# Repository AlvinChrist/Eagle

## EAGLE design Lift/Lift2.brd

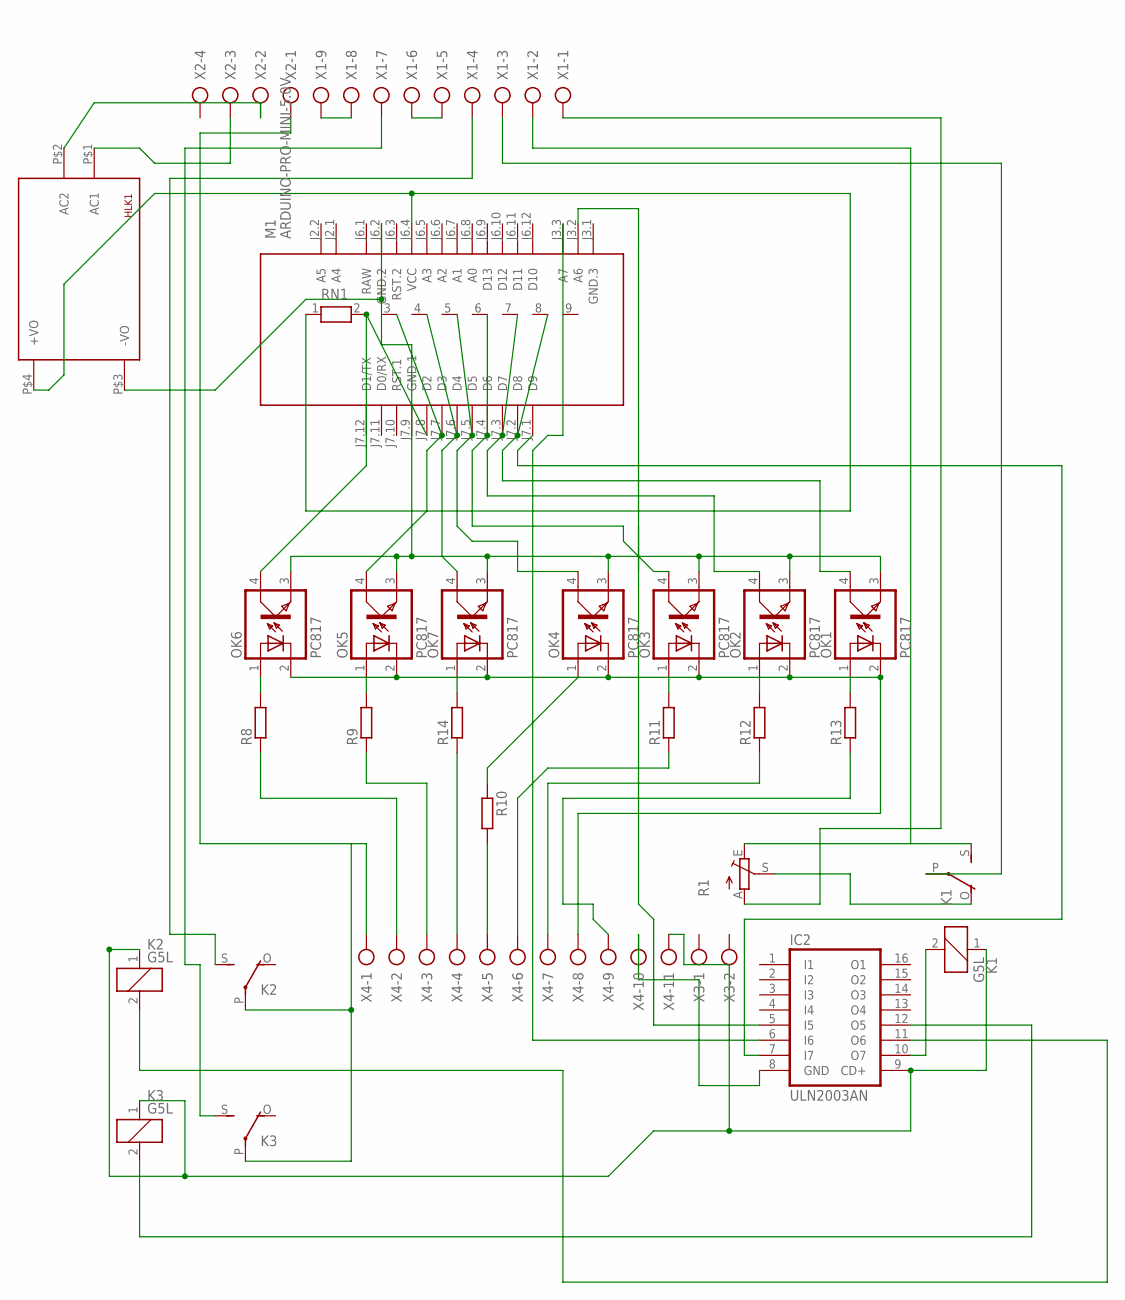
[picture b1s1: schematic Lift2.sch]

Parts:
HLK1: HLK-PM013W; HLK-PM01
IC2: ULN2003AN; DIL16
K1, K2, K3: G5L; G5LE
M1: ARDUINO-PRO-MINI-5.0V; ARDUINO-PRO-MINI
OK1, OK2, OK3, OK4, OK5, OK6, OK7: PC817; DIL04
R1: TRIM_EU-CA6V; CA6V
R8, R9, R10, R11, R12, R13, R14: R-EU_0204/7; 0204/7
RN1: RN08; RN-9
X1: AK300/9
X2: AK300/4
X3: AK300/2
X4: AK300/11

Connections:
5V: HLK1.P$4 (+VO), M1.J6.4 (VCC), RN1.1
12V: IC2.9 (CD+), K1.1, K2.1, K3.1, X4.11
24V: K2.P, K3.P, X2.1, X4.1
GND1: HLK1.P$3 (-VO), M1.J6.2 (GND.2), M1.J7.9 (GND.1), OK1.3 (EMIT), OK2.3 (EMIT), OK3.3 (EMIT), OK4.3 (EMIT), OK5.3 (EMIT), OK6.3 (EMIT), OK7.3 (EMIT)
GND2: OK1.2 (C), OK2.2 (C), OK3.2 (C), OK4.2 (C), OK5.2 (C), OK6.2 (C), OK7.2 (C), X4.8
GND3: IC2.8 (GND), X4.10
L: HLK1.P$1 (AC1), X2.3
N: HLK1.P$2 (AC2), X2.2
unnamed: OK2.1 (A), R12.2
unnamed: OK1.1 (A), R13.2
unnamed: OK3.1 (A), R11.2
unnamed: R10.2, X4.5
unnamed: OK7.1 (A), R14.2
unnamed: R14.1, X4.4
unnamed: IC2.10 (O7), K1.2
unnamed: M1.J7.7 (D3), OK5.4 (COL), RN1.3
unnamed: M1.J7.5 (D5), OK4.4 (COL), RN1.5
unnamed: M1.J7.4 (D6), OK3.4 (COL), RN1.6
unnamed: K1.O, R1.S
unnamed: M1.J7.6 (D4), OK7.4 (COL), RN1.4
unnamed: K1.S, R1.E, X1.2
unnamed: K1.P, X1.3
unnamed: R8.1, X4.2
unnamed: R9.1, X4.3
unnamed: R11.1, X4.6
unnamed: M1.J7.3 (D7), OK2.4 (COL), RN1.7
unnamed: OK5.1 (A), R9.2
unnamed: R13.1, X4.9
unnamed: X1.5, X1.6
unnamed: IC2.12 (O5), K3.2
unnamed: R12.1, X4.7
unnamed: M1.J7.2 (D8), OK1.4 (COL), RN1.8
unnamed: IC2.7 (I7), M1.J7.1 (D9)
unnamed: IC2.11 (O6), K2.2
unnamed: K3.S, X1.7
unnamed: R1.A, X1.1
unnamed: K2.S, X1.4
unnamed: M1.J7.8 (D2), OK6.4 (COL), RN1.2
unnamed: OK6.1 (A), R8.2
unnamed: OK4.1 (A), R10.1
unnamed: IC2.5 (I5), M1.J3.2 (A6)
unnamed: IC2.6 (I6), M1.J3.3 (A7)
unnamed: X1.8, X1.9
RAW: M1.J6.1 (RAW)

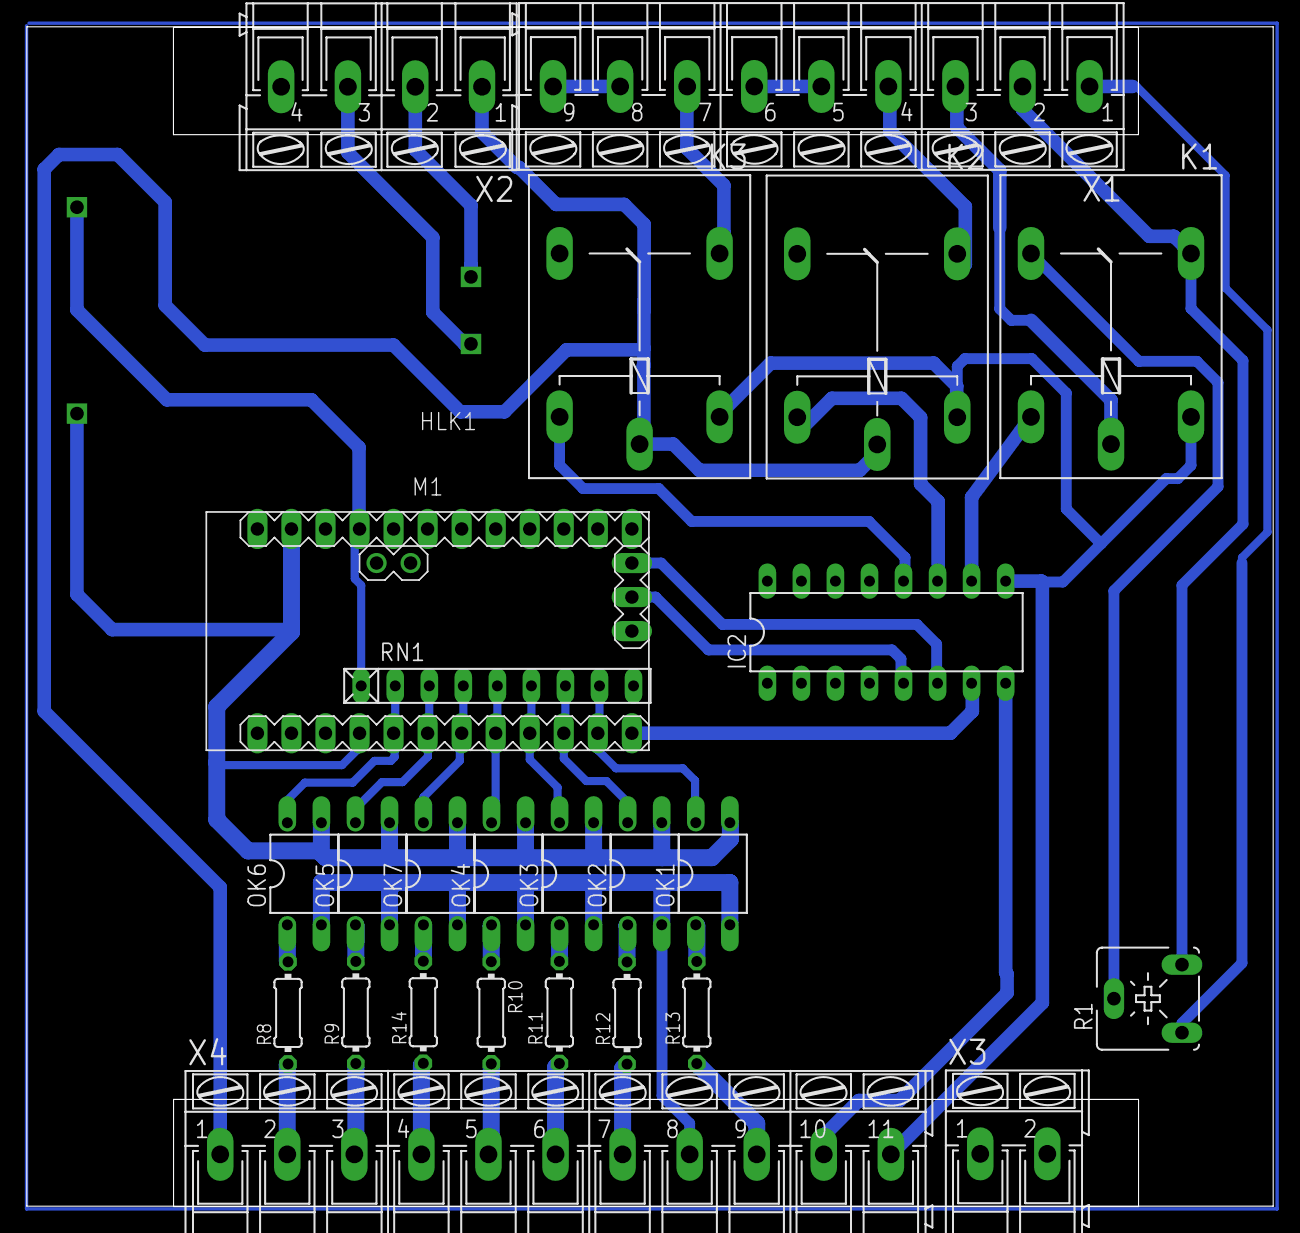
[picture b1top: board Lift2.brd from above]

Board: 2 copper layers, 93.0 x 88.0 mm, 26 parts (0 on the bottom side), 43 nets.

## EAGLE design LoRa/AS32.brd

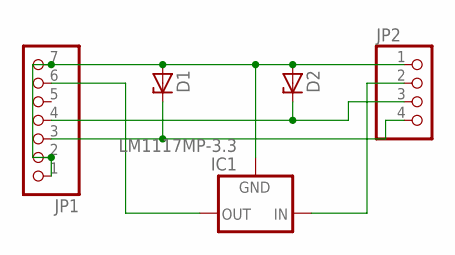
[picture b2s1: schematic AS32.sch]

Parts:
D1, D2: ZENER-DIODEDO35Z10; DO35Z10
IC1: LM1117MP-3.3; SOT223
JP1: PINHD-1X7; 1X07
JP2: PINHD-1X4; 1X04

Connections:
GND: D1.A, D2.A, IC1.1 (GND), JP1.1, JP1.2, JP1.7, JP2.1
unnamed: IC1.3 (IN), JP2.2
unnamed: IC1.2 (OUT), IC1.4 (OUT), JP1.6
unnamed: D2.C, JP1.4, JP2.3
unnamed: D1.C, JP1.3, JP2.4

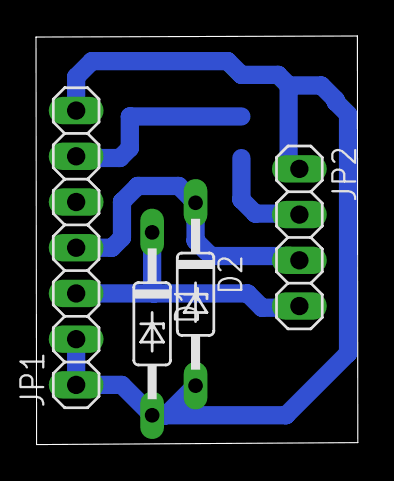
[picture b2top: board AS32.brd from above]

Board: 2 copper layers, 17.9 x 22.7 mm, 5 parts (1 on the bottom side), 5 nets.

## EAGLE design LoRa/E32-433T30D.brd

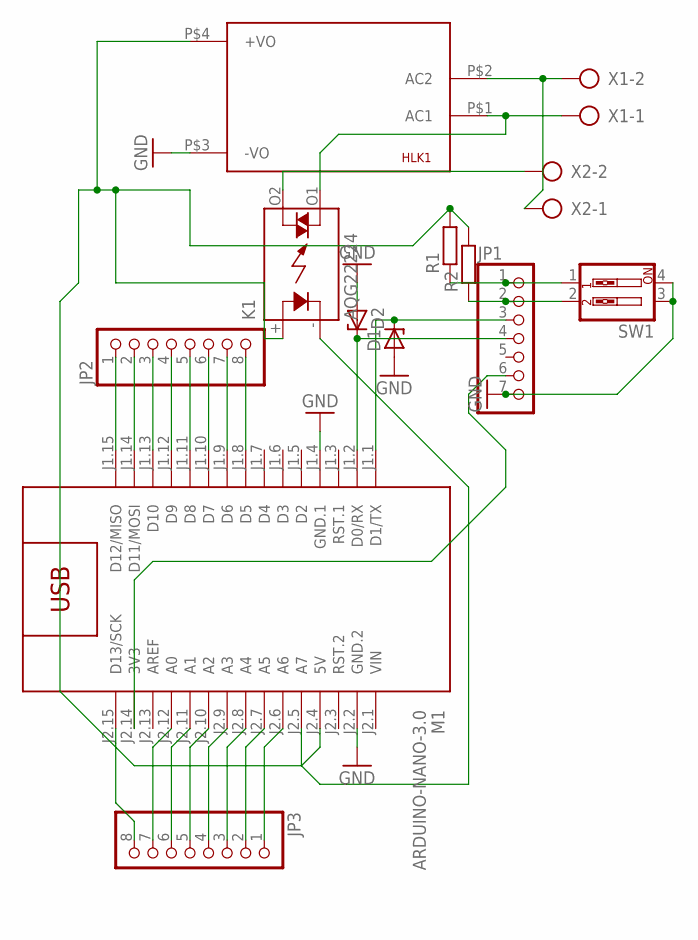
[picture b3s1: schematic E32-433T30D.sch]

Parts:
D1, D2: ZENER-DIODEDO35Z10; DO35Z10
HLK1: HLK-PM013W; HLK-PM01
JP1: PINHD-1X7; 1X07
JP2, JP3: PINHD-1X8; 1X08
K1: AQG22224; AQG
M1: ARDUINO-NANO-3.0
R1, R2: R-EU_0204/7; 0204/7
SW1: SW_DIP-2; EDG-02
X1, X2: AK300/2

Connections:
3.3V: JP1.6, M1.J2.14 (3V3)
5V: HLK1.P$4 (+VO), K1.+ (A), M1.J2.4 (5V), R1.2, R2.2
GND: D1.A, D2.A, HLK1.P$3 (-VO), JP1.7, M1.J1.4 (GND.1), M1.J2.2 (GND.2), SW1.3, SW1.4
unnamed: JP3.7, M1.J2.12 (A0)
unnamed: D2.C, JP1.4, M1.J1.2 (D0/RX)
unnamed: K1.- (K), M1.J2.5 (A7)
unnamed: JP1.2, R2.1, SW1.2
unnamed: JP1.1, R1.1, SW1.1
unnamed: HLK1.P$1 (AC1), K1.O1 (DS2), X1.1
unnamed: HLK1.P$2 (AC2), X1.2, X2.1
unnamed: JP2.8, M1.J1.8 (D5)
unnamed: JP2.7, M1.J1.9 (D6)
unnamed: JP2.6, M1.J1.10 (D7)
unnamed: JP2.5, M1.J1.11 (D8)
unnamed: JP2.4, M1.J1.12 (D9)
unnamed: JP2.3, M1.J1.13 (D10)
unnamed: JP2.2, M1.J1.14 (D11/MOSI)
unnamed: JP2.1, M1.J1.15 (D12/MISO)
unnamed: JP3.8, M1.J2.15 (D13/SCK)
unnamed: JP3.6, M1.J2.11 (A1)
unnamed: JP3.5, M1.J2.10 (A2)
unnamed: JP3.4, M1.J2.9 (A3)
unnamed: D1.C, JP1.3, M1.J1.1 (D1/TX)
unnamed: JP3.3, M1.J2.8 (A4)
unnamed: JP3.2, M1.J2.7 (A5)
unnamed: JP3.1, M1.J2.6 (A6)
unnamed: K1.O2 (DS1), X2.2
VIN: M1.J2.1 (VIN)

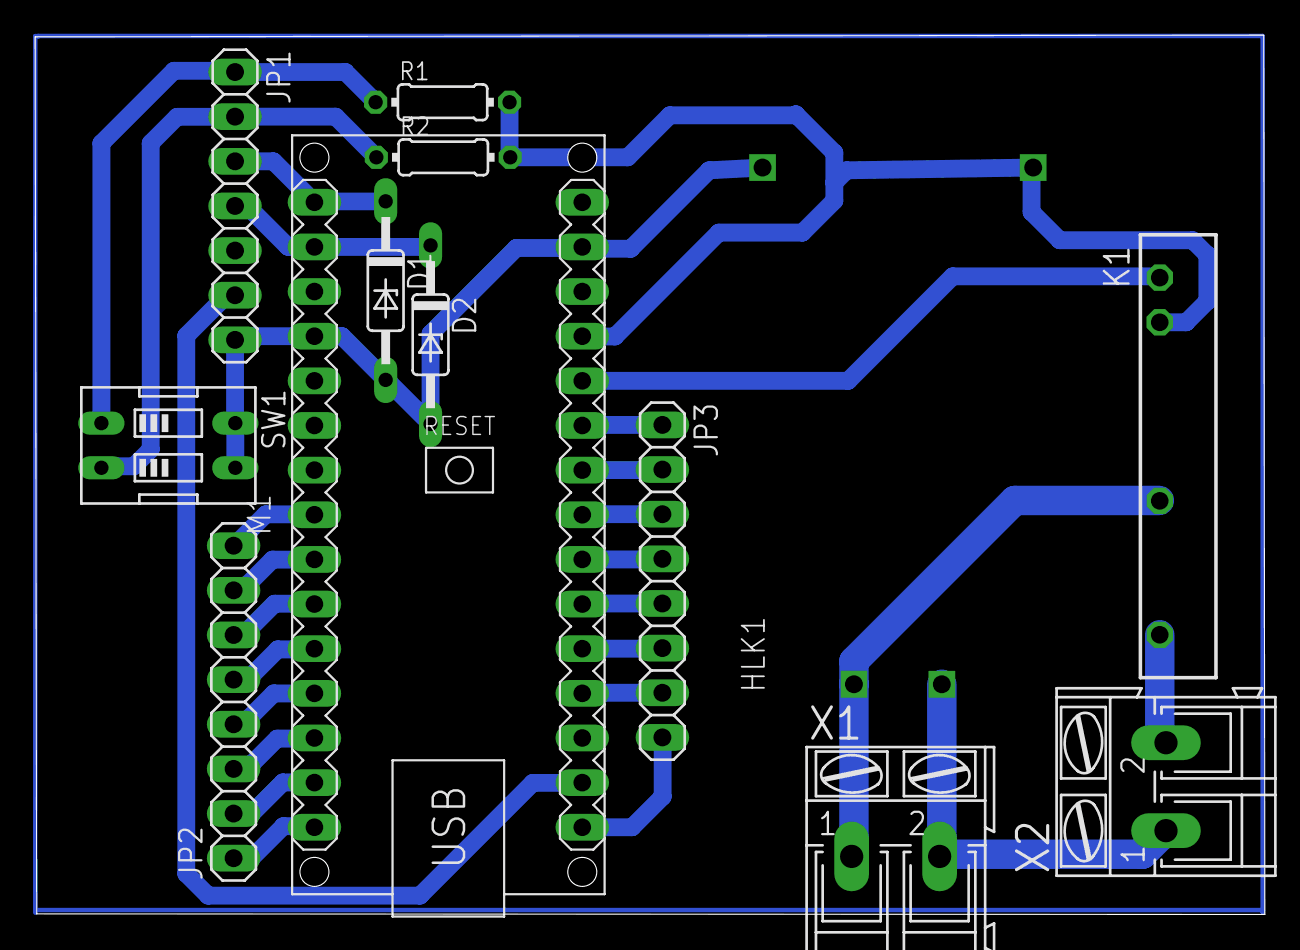
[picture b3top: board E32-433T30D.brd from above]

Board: 2 copper layers, 70.0 x 50.0 mm, 13 parts (0 on the bottom side), 27 nets.

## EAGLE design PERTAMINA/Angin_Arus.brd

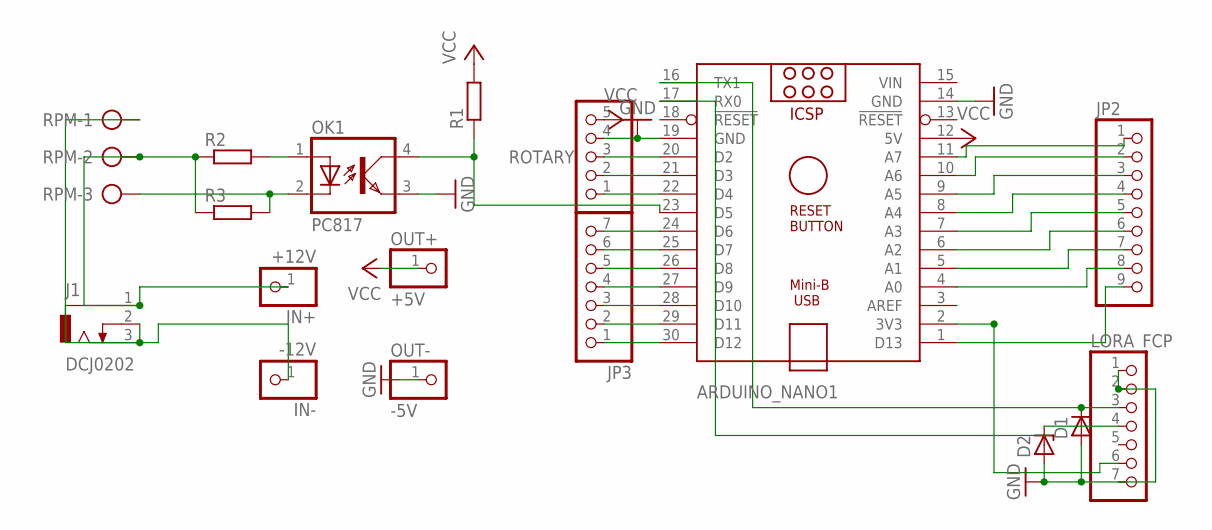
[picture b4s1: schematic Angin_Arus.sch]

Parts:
ARDUINO_NANO1: ARDUINO_NANO
D1, D2: ZENER-DIODEDO35Z10; DO35Z10
IN+: +12V; 1X01
IN-: -12V; 1X01
J1: DCJ0202
JP2: PINHD-1X9; 1X09
JP3: PINHD-1X7; 1X07
LORA_FCP: PINHD-1X7; 1X07
OK1: PC817; DIL04
OUT+: +5V; 1X01
OUT-: -5V; 1X01
R1, R2, R3: R-EU_0204/7; 0204/7
ROTARY: PINHD-1X5; 1X05
RPM: AK300/3

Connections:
3.3V: ARDUINO_NANO1.2 (3V3), LORA_FCP.6
12V: IN+.1, J1.1, R2.1, R3.1, RPM.2
GND: ARDUINO_NANO1.14 (GND), ARDUINO_NANO1.19 (GND), D1.A, D2.A, LORA_FCP.1, LORA_FCP.2, LORA_FCP.7, OK1.3 (EMIT), OUT-.1, ROTARY.4
GND12V: IN-.1, J1.2, J1.3, RPM.1
unnamed: ARDUINO_NANO1.23 (D5), OK1.4 (COL), R1.1
unnamed: OK1.1 (A), R2.2
unnamed: D2.C, LORA_FCP.4
unnamed: ARDUINO_NANO1.20 (D2), ROTARY.3
unnamed: ARDUINO_NANO1.21 (D3), ROTARY.2
unnamed: ARDUINO_NANO1.22 (D4), ROTARY.1
unnamed: ARDUINO_NANO1.8 (A4), JP2.4
unnamed: ARDUINO_NANO1.1 (D13), JP2.9
unnamed: ARDUINO_NANO1.4 (A0), JP2.8
unnamed: ARDUINO_NANO1.5 (A1), JP2.7
unnamed: ARDUINO_NANO1.6 (A2), JP2.6
unnamed: ARDUINO_NANO1.7 (A3), JP2.5
unnamed: ARDUINO_NANO1.9 (A5), JP2.3
unnamed: ARDUINO_NANO1.10 (A6), JP2.2
unnamed: ARDUINO_NANO1.11 (A7), JP2.1
unnamed: ARDUINO_NANO1.30 (D12), JP3.1
unnamed: ARDUINO_NANO1.29 (D11), JP3.2
unnamed: ARDUINO_NANO1.28 (D10), JP3.3
unnamed: ARDUINO_NANO1.27 (D9), JP3.4
unnamed: ARDUINO_NANO1.26 (D8), JP3.5
unnamed: ARDUINO_NANO1.25 (D7), JP3.6
unnamed: ARDUINO_NANO1.24 (D6), JP3.7
RX: ARDUINO_NANO1.16 (TX1), D1.C, LORA_FCP.3
SIGNAL: OK1.2 (C), R3.2, RPM.3
TX: ARDUINO_NANO1.17 (RX0)
VCC: ARDUINO_NANO1.12 (5V), OUT+.1, R1.2, ROTARY.5
VIN: ARDUINO_NANO1.15 (VIN)

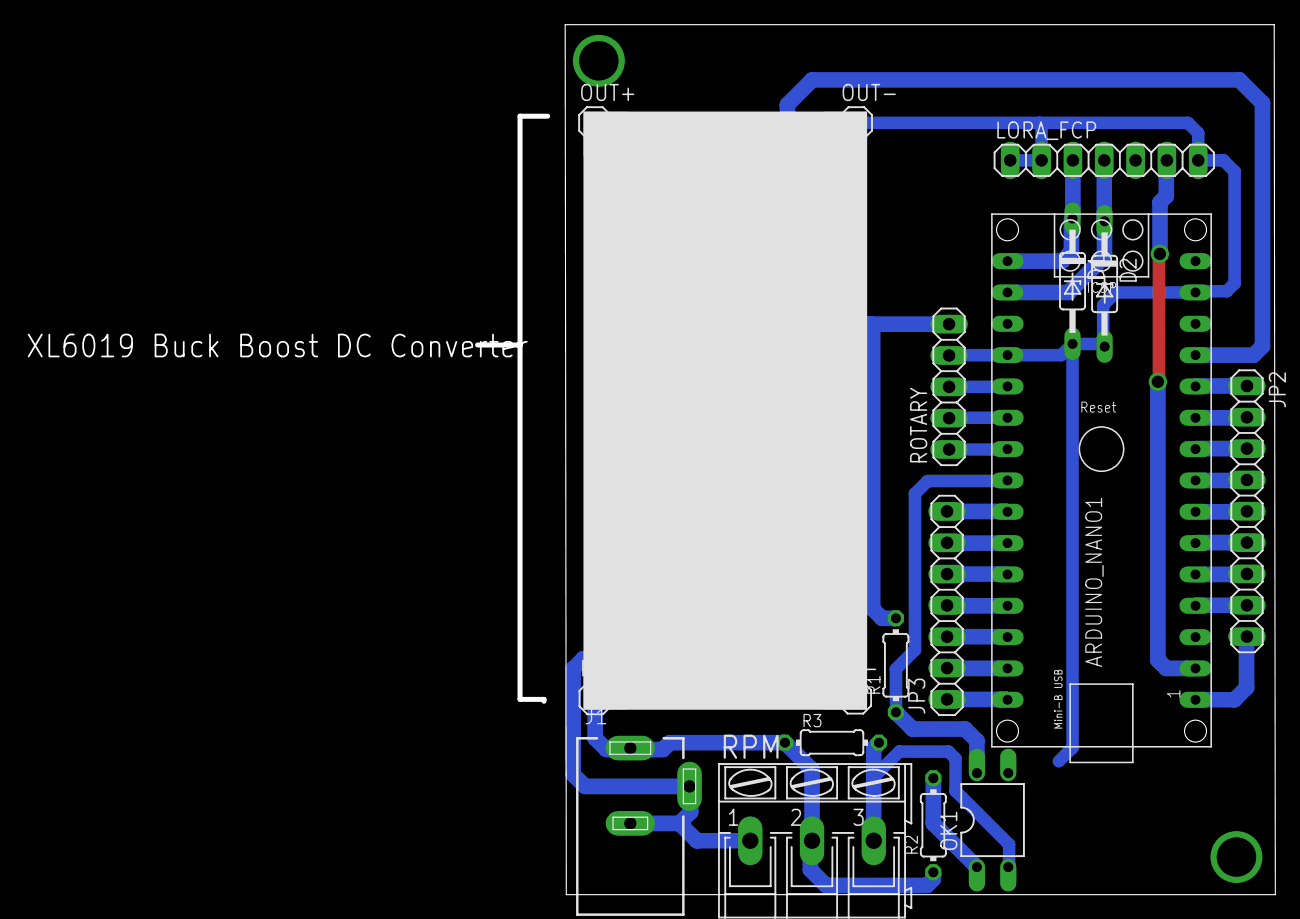
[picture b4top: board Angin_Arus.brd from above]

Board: 2 copper layers, 57.6 x 70.5 mm, 17 parts (0 on the bottom side), 29 nets.

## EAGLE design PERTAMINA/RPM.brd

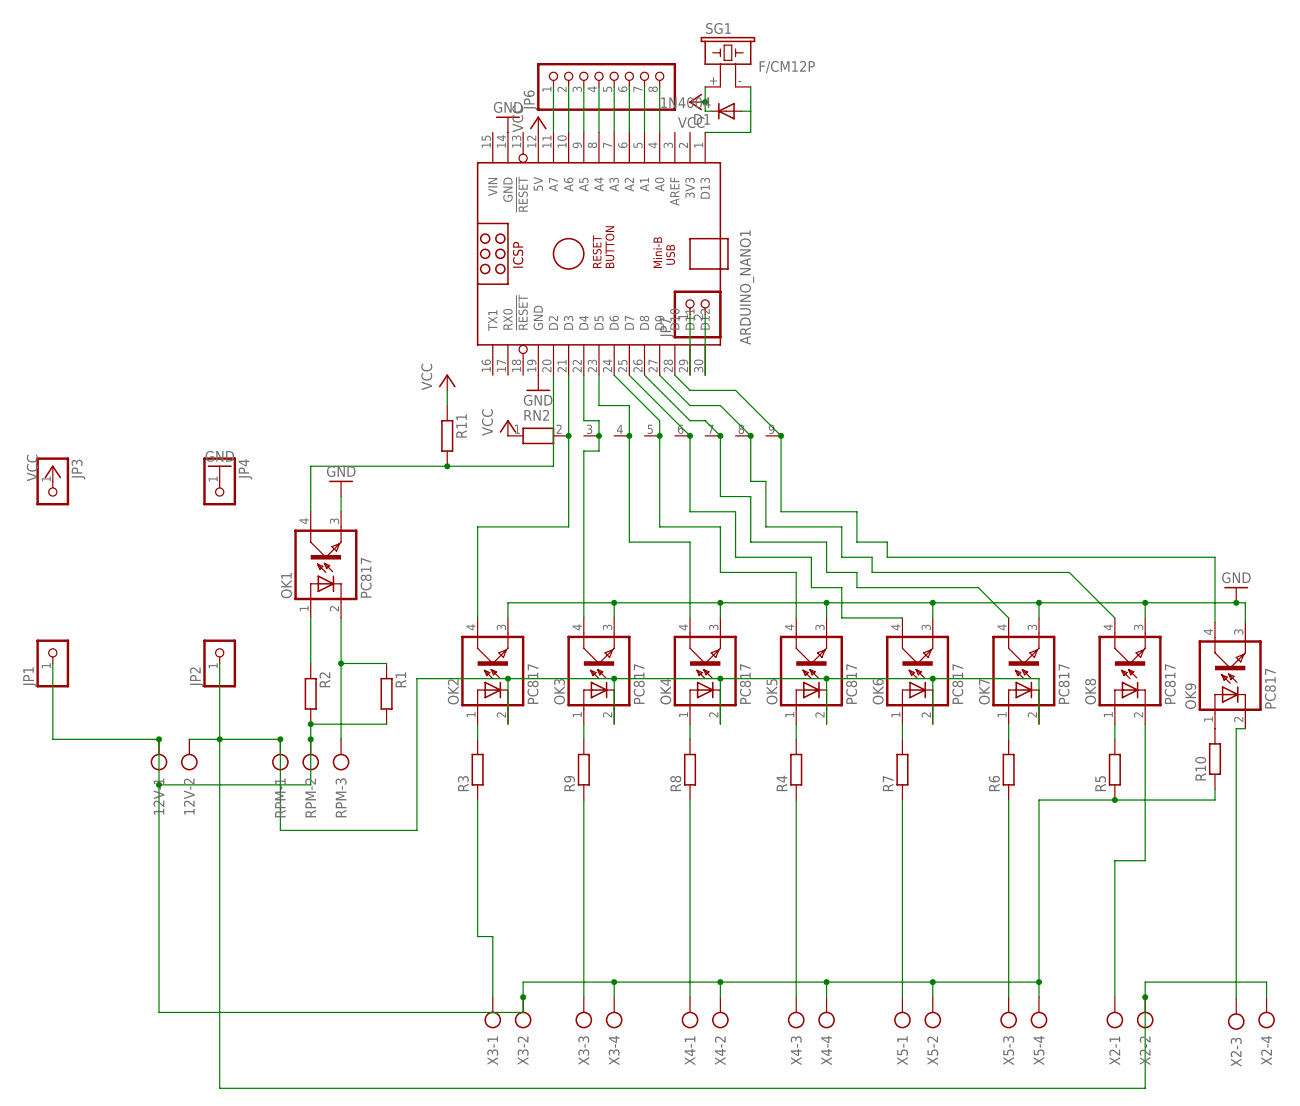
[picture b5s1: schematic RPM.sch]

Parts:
12V: AK300/2
ARDUINO_NANO1: ARDUINO_NANO
D1: 1N4004; DO41-10
JP1, JP2, JP3, JP4: PINHD-1X1; 1X01
JP6: PINHD-1X8; 1X08
JP7: PINHD-1X2; 1X02
OK1, OK2, OK3, OK4, OK5, OK6, OK7, OK8, OK9: PC817; DIL04
R1, R2, R3, R4, R5, R6, R7, R8, R9, R10, R11: R-EU_0204/7; 0204/7
RN2: RN08; RN-9
RPM: AK300/3
SG1: F/CM12P
X2, X3, X4, X5: AK300/4

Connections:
12V: 12V.1, JP1.1, R1.2, R2.2, R5.1, R10.1, RPM.2, X3.2, X3.4, X4.2, X4.4, X5.2, X5.4
GND: ARDUINO_NANO1.14 (GND), ARDUINO_NANO1.19 (GND), JP4.1, OK1.3 (EMIT), OK2.3 (EMIT), OK3.3 (EMIT), OK4.3 (EMIT), OK5.3 (EMIT), OK6.3 (EMIT), OK7.3 (EMIT), OK8.3 (EMIT), OK9.3 (EMIT)
GND12V: 12V.2, JP2.1, OK2.2 (C), OK3.2 (C), OK4.2 (C), OK5.2 (C), OK6.2 (C), OK7.2 (C), RPM.1, X2.2, X2.4
unnamed: ARDUINO_NANO1.20 (D2), OK1.4 (COL), R11.2
unnamed: OK1.1 (A), R2.1
unnamed: ARDUINO_NANO1.23 (D5), OK4.4 (COL), RN2.4
unnamed: ARDUINO_NANO1.26 (D8), OK7.4 (COL), RN2.7
unnamed: OK2.1 (A), R3.2
unnamed: OK3.1 (A), R9.2
unnamed: OK4.1 (A), R8.2
unnamed: OK5.1 (A), R4.2
unnamed: OK6.1 (A), R7.2
unnamed: OK7.1 (A), R6.2
unnamed: R7.1, X5.1
unnamed: ARDUINO_NANO1.29 (D11), JP7.1
unnamed: R4.1, X4.3
unnamed: OK8.2 (C), X2.1
unnamed: R3.1, X3.1
unnamed: R9.1, X3.3
unnamed: ARDUINO_NANO1.30 (D12), JP7.2
unnamed: ARDUINO_NANO1.11 (A7), JP6.1
unnamed: ARDUINO_NANO1.27 (D9), OK8.4 (COL), RN2.8
unnamed: ARDUINO_NANO1.28 (D10), OK9.4 (COL), RN2.9
unnamed: R8.1, X4.1
unnamed: ARDUINO_NANO1.10 (A6), JP6.2
unnamed: ARDUINO_NANO1.21 (D3), OK2.4 (COL), RN2.2
unnamed: ARDUINO_NANO1.22 (D4), OK3.4 (COL), RN2.3
unnamed: OK9.2 (C), X2.3
unnamed: OK8.1 (A), R5.2
unnamed: ARDUINO_NANO1.25 (D7), OK6.4 (COL), RN2.6
unnamed: ARDUINO_NANO1.9 (A5), JP6.3
unnamed: ARDUINO_NANO1.1 (D13), D1.A, SG1.- (2)
unnamed: ARDUINO_NANO1.8 (A4), JP6.4
unnamed: ARDUINO_NANO1.7 (A3), JP6.5
unnamed: ARDUINO_NANO1.6 (A2), JP6.6
unnamed: ARDUINO_NANO1.5 (A1), JP6.7
unnamed: ARDUINO_NANO1.4 (A0), JP6.8
unnamed: ARDUINO_NANO1.24 (D6), OK5.4 (COL), RN2.5
unnamed: OK9.1 (A), R10.2
unnamed: R6.1, X5.3
SIGNAL: OK1.2 (C), R1.1, RPM.3
VCC: ARDUINO_NANO1.12 (5V), D1.C, JP3.1, R11.1, RN2.1, SG1.+ (1)
VIN: ARDUINO_NANO1.15 (VIN)

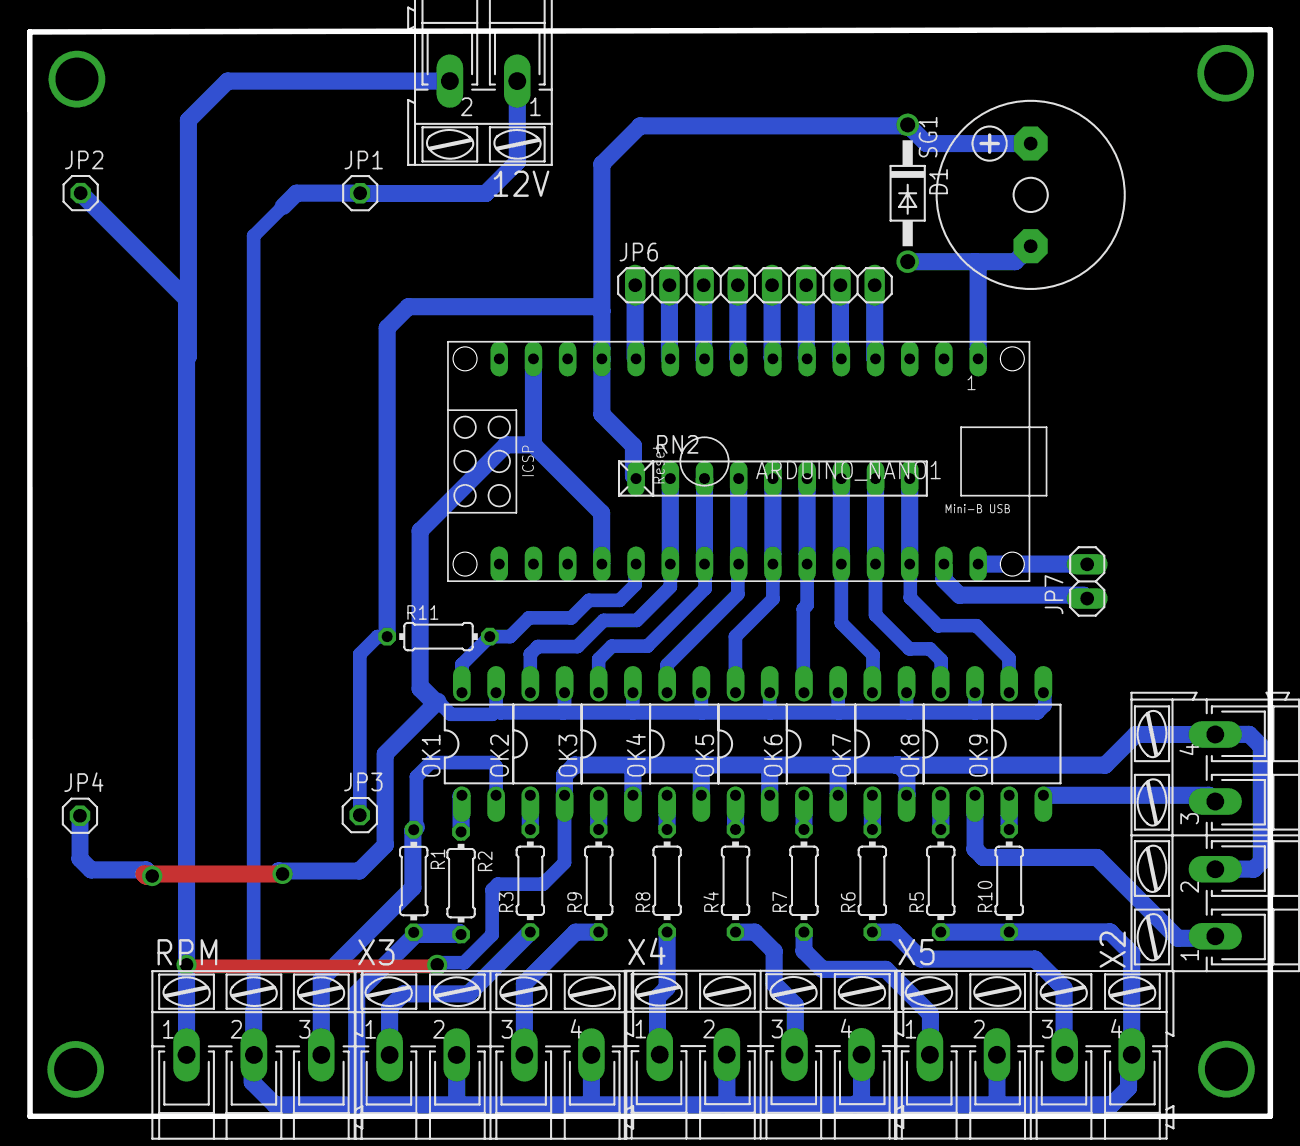
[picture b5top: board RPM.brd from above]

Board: 2 copper layers, 92.1 x 80.7 mm, 36 parts (0 on the bottom side), 42 nets.

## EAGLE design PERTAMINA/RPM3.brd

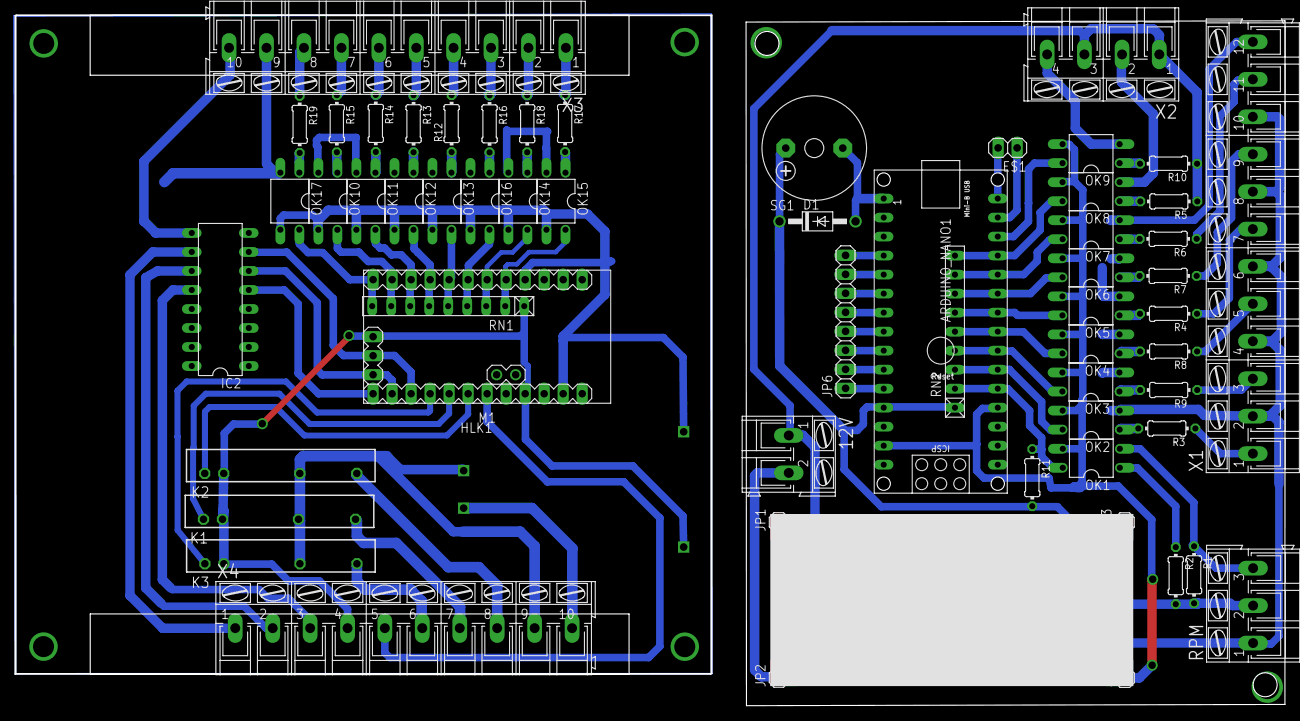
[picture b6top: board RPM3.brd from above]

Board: 2 copper layers, 169.7 x 92.3 mm, 59 parts (0 on the bottom side), 85 nets.

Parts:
12V: AK300/2
ARDUINO_NANO1: ARDUINO_NANO
D1: 1N4004; DO41-10
E$1: 1X02
HLK1: HLK-PM013W; HLK-PM01
IC2: ULN2003AN; DIL16
JP1, JP2, JP3, JP4: 1X01
JP6: 1X08
K1, K2, K3: AQG12105; AQG
M1: ARDUINO-PRO-MINI-5.0V; ARDUINO-PRO-MINI
OK1, OK2, OK3, OK4, OK5, OK6, OK7, OK8, OK9, OK10, OK11, OK12, OK13, OK14, OK15, OK16, OK17: PC817; DIL04
R1, R2, R3, R4, R5, R6, R7, R8, R9, R10, R11, R12, R13, R14, R15, R16, R17, R18, R19: 0204/7
RN1, RN2: RN-9
RPM: AK300/3
SG1: F/CM12P
X1: AK300/12
X2: AK300/4
X3, X4: AK300/10

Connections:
5V: HLK1.P$4, K1.+, K2.+, K3.+, M1.J6.4, RN1.1, X4.4
12V: IC2.9, X3.10
GND: ARDUINO_NANO1.14, ARDUINO_NANO1.19, JP4.1, OK1.3, OK2.3, OK3.3, OK4.3, OK5.3, OK6.3, OK7.3, OK8.3, OK9.3
GND1: HLK1.P$3, M1.J6.2, M1.J7.9, OK10.3, OK11.3, OK12.3, OK13.3, OK14.3, OK15.3, OK16.3, OK17.3
GND12V: IC2.8, OK10.2, OK11.2, OK12.2, OK13.2, OK14.2, OK15.2, OK16.2, OK17.2, X3.9
unnamed: ARDUINO_NANO1.20, OK1.4, R11.1, RN2.2
unnamed: OK1.1, R2.1
unnamed: M1.J7.5, OK13.4, RN1.5
unnamed: M1.J7.6, OK16.4, RN1.4
unnamed: OK2.1, R3.2
unnamed: OK3.1, R9.2
unnamed: OK4.1, R8.2
unnamed: OK5.1, R4.2
unnamed: OK6.1, R7.2
unnamed: OK7.1, R6.2
unnamed: R7.1, X1.9
unnamed: ARDUINO_NANO1.29, E$1.1
unnamed: R4.1, X1.7
unnamed: R17.1, X3.1
unnamed: R3.1, X1.1
unnamed: R9.1, X1.3
unnamed: ARDUINO_NANO1.30, E$1.2
unnamed: ARDUINO_NANO1.11, JP6.1
unnamed: R18.1, X3.2
unnamed: R15.1, X3.7
unnamed: R8.1, X1.5
unnamed: ARDUINO_NANO1.10, JP6.2
unnamed: ARDUINO_NANO1.21, OK2.4, RN2.3
unnamed: ARDUINO_NANO1.22, OK3.4, RN2.4
unnamed: ARDUINO_NANO1.23, OK4.4, RN2.5
unnamed: ARDUINO_NANO1.24, OK5.4, RN2.6
unnamed: ARDUINO_NANO1.25, OK6.4, RN2.7
unnamed: ARDUINO_NANO1.26, OK7.4, RN2.8
unnamed: ARDUINO_NANO1.9, JP6.3
unnamed: ARDUINO_NANO1.27, OK8.4, RN2.9
unnamed: ARDUINO_NANO1.1, D1.A, SG1.-
unnamed: ARDUINO_NANO1.8, JP6.4
unnamed: ARDUINO_NANO1.7, JP6.5
unnamed: ARDUINO_NANO1.6, JP6.6
unnamed: ARDUINO_NANO1.5, JP6.7
unnamed: ARDUINO_NANO1.4, JP6.8
unnamed: R13.1, X3.5
unnamed: OK9.1, R10.2
unnamed: OK8.1, R5.2
unnamed: R6.1, X1.11
unnamed: 12V.2, JP2.1, OK2.2, OK3.2, OK4.2, OK5.2, OK6.2, OK7.2, RPM.1, X1.2, X1.4, X1.6, X1.8, X1.10, X1.12
unnamed: 12V.1, JP1.1, R1.2, R2.2, R5.1, R10.1, RPM.2, X2.1, X2.3
unnamed: OK8.2, X2.2
unnamed: R14.1, X3.6
unnamed: OK9.2, X2.4
unnamed: M1.J7.3, OK11.4, RN1.7
unnamed: M1.J7.7, OK14.4, RN1.3
unnamed: M1.J7.2, OK10.4, RN1.8
unnamed: IC2.5, M1.J6.12
unnamed: OK13.1, R12.1
unnamed: R16.1, X3.3
unnamed: IC2.7, M1.J6.10
unnamed: M1.J7.8, OK15.4, RN1.2
unnamed: IC2.6, M1.J6.11
unnamed: M1.J7.4, OK12.4, RN1.6
unnamed: OK10.1, R15.2
unnamed: OK11.1, R14.2
unnamed: OK12.1, R13.2
unnamed: R12.2, X3.4
unnamed: OK16.1, R16.2
unnamed: OK14.1, R18.2
unnamed: OK15.1, R17.2
unnamed: IC2.10, X4.1
unnamed: IC2.11, X4.2
unnamed: IC2.12, X4.3
unnamed: HLK1.P$2, X4.10
unnamed: HLK1.P$1, K1.O1, K2.O1, K3.O1, X4.9
unnamed: OK17.1, R19.2
unnamed: R19.1, X3.8
unnamed: K3.O2, X4.6
unnamed: K1.O2, X4.7
unnamed: K2.O2, X4.8
unnamed: M1.J7.1, OK17.4, RN1.9
unnamed: M1.J6.6, X4.5
unnamed: K3.-, M1.J6.9
unnamed: K1.-, M1.J6.8
unnamed: K2.-, M1.J6.7
S$1: ARDUINO_NANO1.28, OK9.4
SIGNAL: OK1.2, R1.1, RPM.3
VCC: ARDUINO_NANO1.12, D1.C, JP3.1, R11.2, RN2.1, SG1.+

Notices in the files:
parts and their libraries:
diy-modules: Released under the Creative Commons Attribution 4.0 International License: http://creativecommons.org/licenses/by/4.0
lm1117: (c) 2014 Samuel Lourenço
